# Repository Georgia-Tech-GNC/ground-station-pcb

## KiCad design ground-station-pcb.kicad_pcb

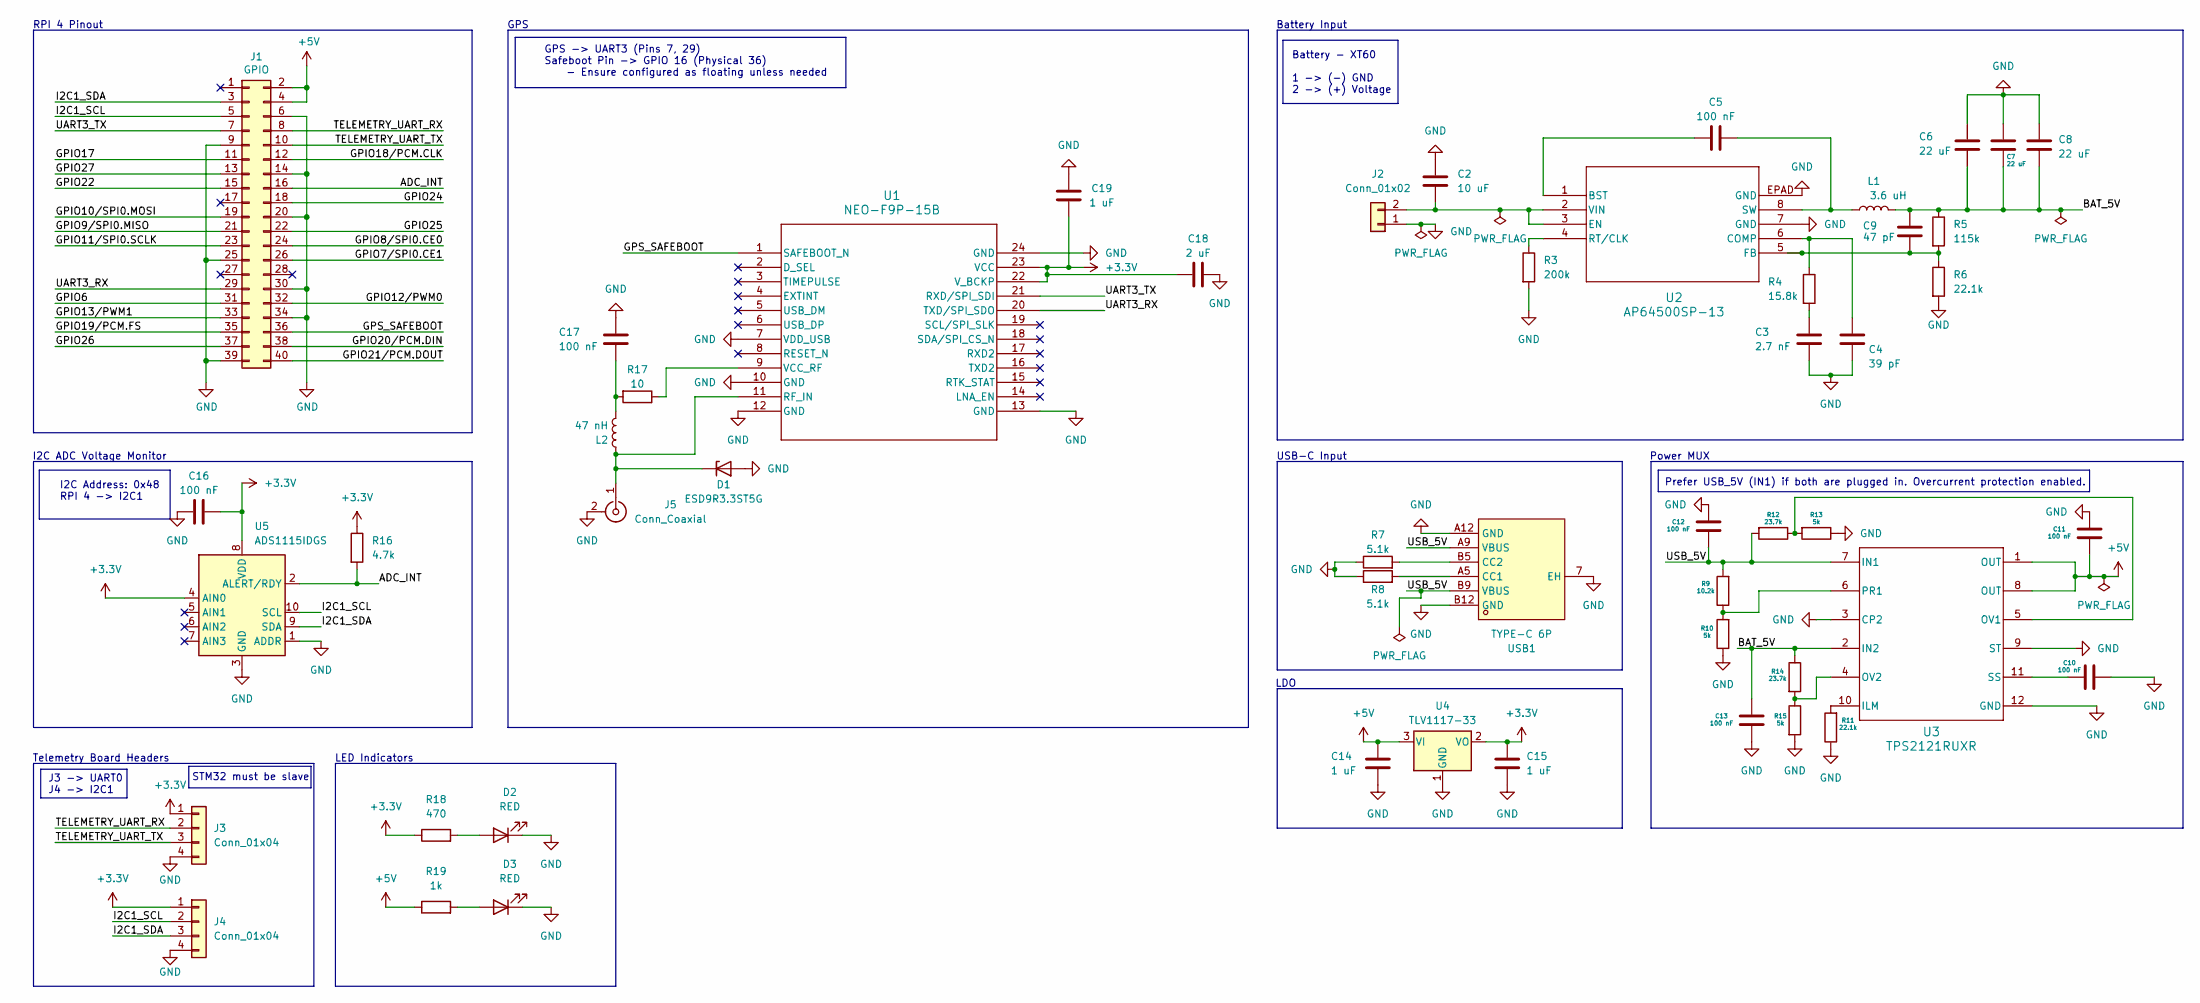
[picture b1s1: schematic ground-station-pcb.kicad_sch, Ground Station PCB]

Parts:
C2: 10 uF; C_0805_2012Metric; Voltage Rating 50V; Tolerance 10%
C3: 2.7 nF; C_0805_2012Metric; Tolerance 10%; Voltage Rating 16V
C4: 39 pF; C_0805_2012Metric; Tolerance 10%; Voltage Rating 16V
C5, C10, C11, C12, C13, C16: 100 nF; C_0805_2012Metric; Tolerance 10%; Voltage Rating 16V
C6, C7, C8: 22 uF; C_0805_2012Metric; Tolerance 10%; Voltage Rating 16V
C9: 47 pF; C_0805_2012Metric; Tolerance 10%; Voltage Rating 16V
C14, C15: 1 uF; C_0805_2012Metric; Voltage Rating 16V; Tolerance 10%
C17: 100 nF; C_0805_2012Metric; Voltage Rating 16V; Tolerance 10%
C18: 2 uF; C_0805_2012Metric; Tolerance 10%; Voltage Rating 16V
C19: 1 uF; C_0805_2012Metric; Tolerance 10%; Voltage Rating 16V
D1: ESD9R3.3ST5G; D_SOD-923; MPN ESD9R3.3ST5G
D2, D3: RED; LED_0603_1608Metric
J1: GPIO; PinSocket_2x20_P2.54mm_Vertical
J2: Conn_01x02; AMASS_XT60IPW-M_1x03_P7.20mm_Horizontal
J3, J4: Conn_01x04; PinSocket_1x04_P2.54mm_Vertical
J5: Conn_Coaxial; SMA_Molex_73251-2120_EdgeMount_Horizontal; MPN 73251-1150
L1: 3.6 uH; L_Bourns-SRN8040_8x8.15mm; MPN SRN8040HA-3R6M
L2: 47 nH; L_0402_1005Metric_Pad0.77x0.64mm_HandSolder; MPN LQG15HS47NJ02
R3: 200k; R_0805_2012Metric; Tolerance 1%; Power Rating 0.1W
R4: 15.8k; R_0805_2012Metric; Tolerance 1%; Power Rating 0.1W
R5: 115k; R_0805_2012Metric; Tolerance 1%; Power Rating 0.1W
R6, R11: 22.1k; R_0805_2012Metric; Tolerance 1%; Power Rating 0.1W
R7, R8: 5.1k; R_0805_2012Metric; Tolerance 1%; Power Rating 0.1W
R9: 10.2k; R_0805_2012Metric; Tolerance 1%; Power Rating 0.1W
R10, R13, R15: 5k; R_0805_2012Metric; Tolerance 1%; Power Rating 0.1W
R12, R14: 23.7k; R_0805_2012Metric; Tolerance 1%; Power Rating 0.1W
R16: 4.7k; R_0805_2012Metric; Tolerance 1%; Power Rating 0.1W
R17: 10; R_0805_2012Metric; Tolerance 1%; Power Rating 0.1W
R18: 470; R_0805_2012Metric; Tolerance 1%; Power Rating 0.1W
R19: 1k; R_0805_2012Metric; Tolerance 1%; Power Rating 0.1W
U1: NEO-F9P-15B; MOD24_NEO-F9P-15B_UBL; MPN NEO-F9P-15B
U2: AP64500SP-13; SO-8EP_DIO; MPN AP64500SP-13
U3: TPS2121RUXR; RUX0012A; MPN TPS2121RUXR
U4: TLV1117-33; SOT-223-3_TabPin2; MPN TLV1117LV33DCYR
U5: ADS1115IDGS; TSSOP-10_3x3mm_P0.5mm; MPN ADS1115IDGSR
USB1: TYPE-C 6P; TYPE-C-SMD_TYPE-C-6P_1; MPN TYPE-C 6P

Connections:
+3.3V: C15.1, C16.2, C18.1, C19.1, J3.1, J4.1, R16.1, R18.1, U1.22 (V_BCKP), U1.23 (VCC), U4.2 (VO), U5.4 (AIN0), U5.8 (VDD)
+5V: C11.1, C14.1, J1.2, J1.4, R19.1, U3.1 (OUT), U3.8 (OUT), U4.3 (VI)
/ADC_INT: J1.16, R16.2, U5.2 (ALERT/RDY)
/BAT_5V: C6.2, C7.2, C8.2, C9.1, C13.2, L1.2, R5.1, R14.1, U3.2 (IN2)
/GPIO6: J1.31
/GPIO7/SPI0.CE1: J1.26
/GPIO8/SPI0.CE0: J1.24
/GPIO9/SPI0.MISO: J1.21
/GPIO10/SPI0.MOSI: J1.19
/GPIO11/SPI0.SCLK: J1.23
/GPIO12/PWM0: J1.32
/GPIO13/PWM1: J1.33
/GPIO17: J1.11
/GPIO18/PCM.CLK: J1.12
/GPIO19/PCM.FS: J1.35
/GPIO20/PCM.DIN: J1.38
/GPIO21/PCM.DOUT: J1.40
/GPIO22: J1.15
/GPIO24: J1.18
/GPIO25: J1.22
/GPIO26: J1.37
/GPIO27: J1.13
/GPS_SAFEBOOT: J1.36, U1.1 (SAFEBOOT_N)
/I2C1_SCL: J1.5, J4.2, U5.10 (SCL)
/I2C1_SDA: J1.3, J4.3, U5.9 (SDA)
/TELEMETRY_UART_RX: J1.8, J3.2
/TELEMETRY_UART_TX: J1.10, J3.3
/UART3_RX: J1.29, U1.20 (TXD/SPI_SDO)
/UART3_TX: J1.7, U1.21 (RXD/SPI_SDI)
/USB_5V: C12.1, R9.2, R12.2, U3.7 (IN1), USB1.A9 (VBUS), USB1.B9 (VBUS)
GND: C2.1, C3.2, C4.2, C6.1, C7.1, C8.1, C10.2, C11.2, C12.2, C13.1, C14.2, C15.2, C16.1, C17.2, C18.2, C19.2, D1.2 (A), D2.1 (K), D3.1 (K), J1.6, J1.9, J1.14, J1.20, J1.25, J1.30, J1.34, J1.39, J2.1, J3.4, J4.4, J5.2 (Ext), R3.2, R6.2, R7.1, R8.1, R10.1, R11.1, R13.1, R15.2, U1.7 (VDD_USB), U1.10 (GND), U1.12 (GND), U1.13 (GND), U1.24 (GND), U2.7 (GND), U2.EPAD (GND), U3.3 (CP2), U3.9 (ST), U3.12 (GND), U4.1 (GND), U5.1 (ADDR), U5.3 (GND), USB1.7 (EH), USB1.A12 (GND), USB1.B12 (GND)
unnamed: C3.1, R4.2
unnamed: C17.1, L2.2, R17.2
unnamed: D1.1 (K), J5.1 (In), L2.1, U1.11 (RF_IN)
unnamed: D2.2 (A), R18.2
unnamed: D3.2 (A), R19.2
unnamed: C2.2, J2.2, U2.2 (VIN), U2.3 (EN)
unnamed: R17.1, U1.9 (VCC_RF)
unnamed: C5.1, U2.1 (BST)
unnamed: C4.1, R4.1, U2.6 (COMP)
unnamed: C9.2, R5.2, R6.1, U2.5 (FB)
unnamed: R3.1, U2.4 (RT/CLK)
unnamed: C5.2, L1.1, U2.8 (SW)
unnamed: R11.2, U3.10 (ILM)
unnamed: R12.1, R13.2, U3.5 (OV1)
unnamed: R14.2, R15.1, U3.4 (OV2)
unnamed: R9.1, R10.2, U3.6 (PR1)
unnamed: C10.1, U3.11 (SS)
unnamed: R8.2, USB1.A5 (CC1)
unnamed: R7.2, USB1.B5 (CC2)

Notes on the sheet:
USB-C Input
Telemetry Board Headers
LDO
I2C Address: 0x48 RPI 4 -> I2C1
Prefer USB_5V (IN1) if both are plugged in. Overcurrent protection enabled.
STM32 must be slave
Power MUX
GPS -> UART3 (Pins 7, 29) Safeboot Pin -> GPIO 16 (Physical 36) - Ensure configured as floating unless needed
I2C ADC Voltage Monitor
J3 -> UART0 J4 -> I2C1
LED Indicators
RPI 4 Pinout
Battery Input
GPS
Battery - XT60 1 -> (-) GND 2 -> (+) Voltage

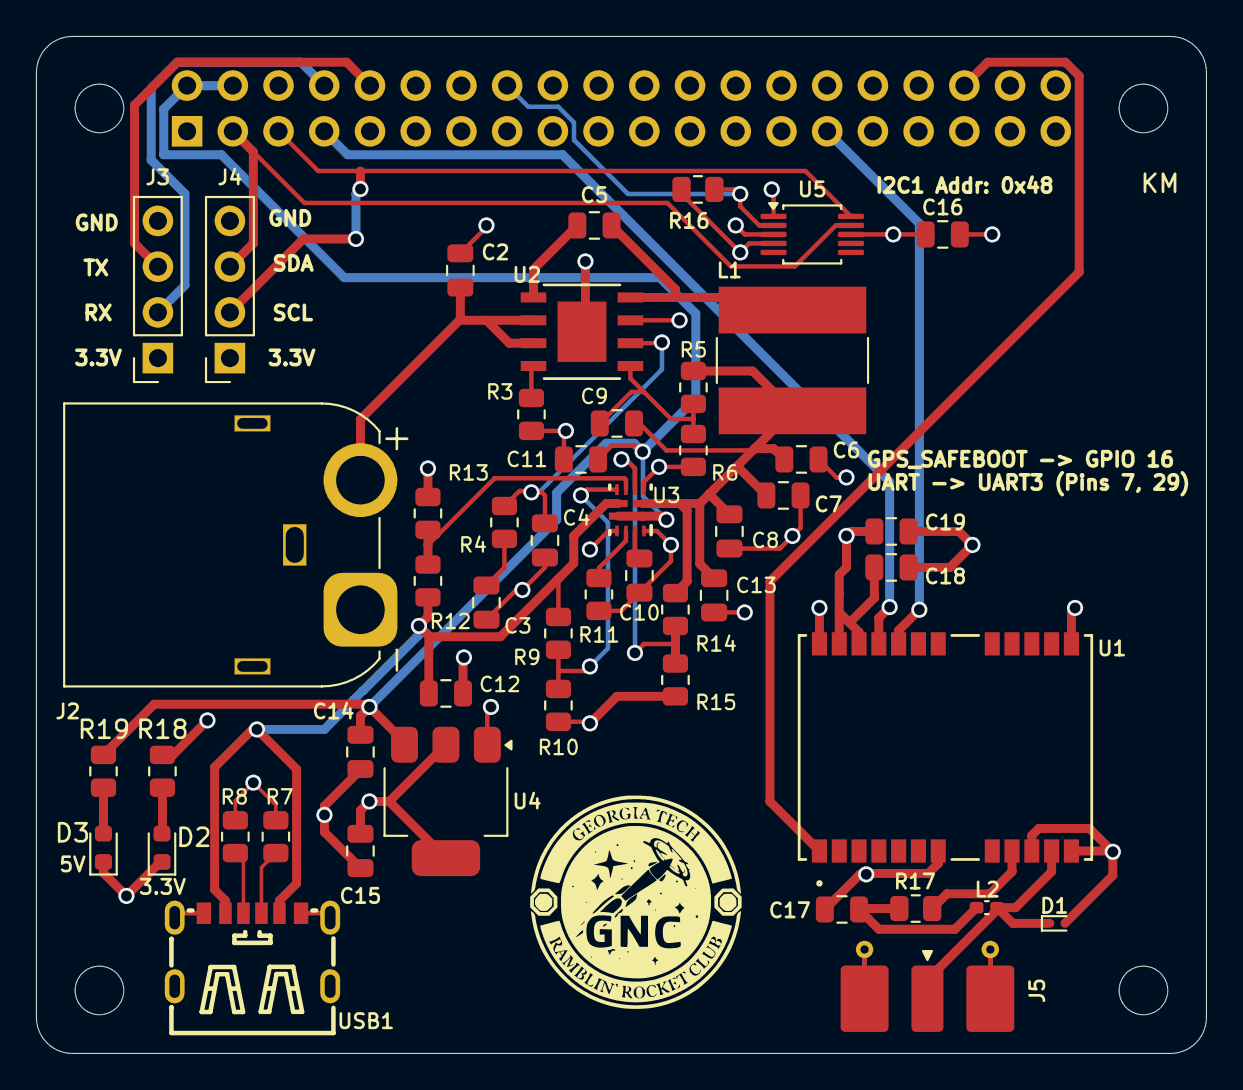
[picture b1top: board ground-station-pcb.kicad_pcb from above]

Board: 4 copper layers, 65.0 x 56.5 mm, 55 parts (1 on the bottom side), 32 nets.

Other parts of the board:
MH1, MH2, MH3, MH4: MountingHole_2.7mm_M2.5
